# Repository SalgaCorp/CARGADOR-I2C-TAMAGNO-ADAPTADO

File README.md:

# CARGADOR-TAMAÑO-ADAPTADO

**Objetivos**:

1.- Open Source.

2.- Que el tamaño sea similar al cargador TP4056 para usar en proyectos ya existentes.

3.- Que tenga monitoreo de variables de batería: voltaje, %carga, etc.

# **Contenido del repositorio**:

PCB
Datasheet
Fotos

# *Documentation*:

Usa los siguientes componentes importantes:

Datasheet (BQ24075 Charger)

[bq24075.pdf](https://github.com/SalgaCorp/CARGADOR-TAMAGNO-ADAPTADO/files/10971589/bq24075.pdf)

Datasheet (BQ27441-G1 Fuel Gauge)

[bq27441-g1.pdf](https://github.com/SalgaCorp/CARGADOR-TAMAGNO-ADAPTADO/files/10971591/bq27441-g1.pdf)

Para monitoreo de variables de batería usar la siguiente libreria y ejemplos de cortesia de SpurkFun:  

https://github.com/sparkfun/SparkFun_BQ27441_Arduino_Library

Comparacion de PCB con tamaño del cargador TP4056

# Product Versions: DEMO

Luego subiré la pcb armada completamente.

# License Information
This product is open source!

# Contact Us
Call or WhatsApp 
https://api.whatsapp.com/send?phone=56966814899

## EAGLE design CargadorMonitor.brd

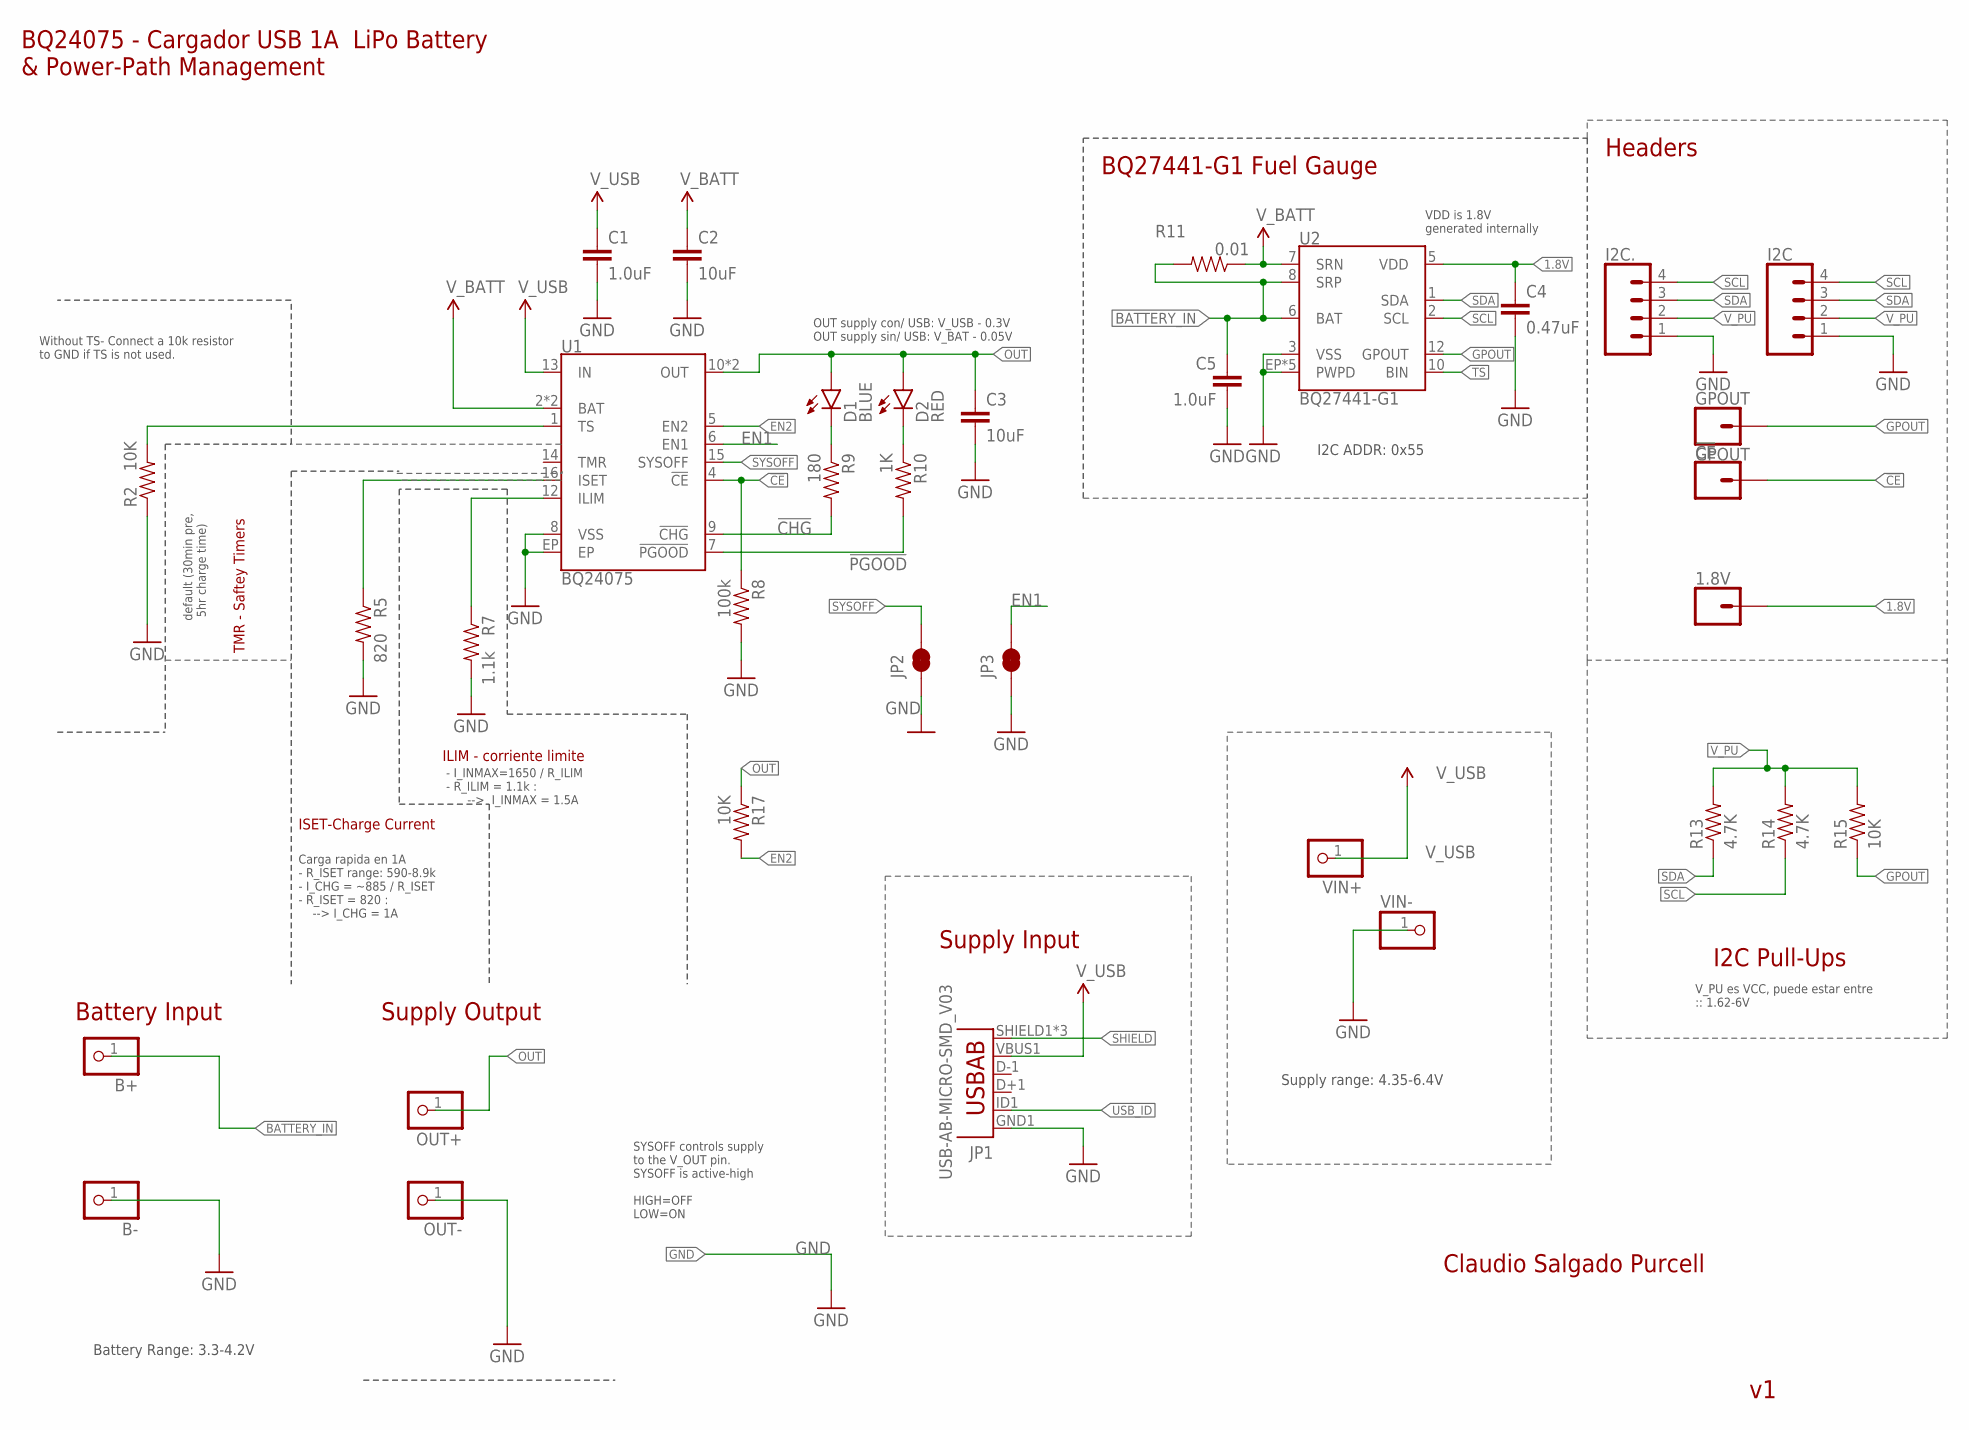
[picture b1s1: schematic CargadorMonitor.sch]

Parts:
1.8V: CONN_01PTH_NO_SILK_SMALL; 1X01_SMALL
!CE!: CONN_01PTH_NO_SILK_SMALL; 1X01_SMALL
B+: PINHD-1X1; 1X01
B-: PINHD-1X1; 1X01
C1: 1.0uF; 1206-CAP
C2, C3: 10uF; 0805-CAP
C4: 0.47uF; 0603-CAP
C5: 1.0uF; 0603-CAP
D1: BLUE; LED-0603
D2: RED; LED-0603
GPOUT: GPOUT; 1X01_SMALL
I2C: CONN_04SMD2; JST04_1MM_RA
I2C.: CONN_041.27MM; 1X04_1.27MM
JP1: USB-AB-MICRO-SMD_V03
JP2, JP3: JUMPER-SMT_2_NC_TRACE_SILK; SMT-JUMPER_2_NC_TRACE_SILK
OUT+: PINHD-1X1; 1X01
OUT-: PINHD-1X1; 1X01
R2, R15, R17: 10K; 0603-RES
R5: 820; 0603-RES
R7: 1.1k; 0603-RES
R8: 100k; 0603-RES
R9: 180; 0603-RES
R10: 1K; 0603-RES
R11: 0.01; 1206
R13, R14: 4.7K; 0603-RES
U1: BQ24075; PVQFN-N16
U2: BQ27441-G1; PDSO-N12
VIN+: PINHD-1X1; 1X01
VIN-: PINHD-1X1; 1X01

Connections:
1.8V: 1.8V.P$1, C4.1, U2.5 (VDD)
!CE!: !CE!.P$1, R8.1, U1.4 (!CE!)
!CHG!: R9.2, U1.9 (!CHG!)
!PGOOD!: R10.2, U1.7 (!PGOOD!)
BATTERY_IN: B+.1, C5.1, R11.2, U2.6 (BAT), U2.8 (SRP)
EN1: JP3.2, U1.6 (EN1)
EN2: R17.2, U1.5 (EN2)
GND: B-.1, C1.2, C2.2, C3.2, C4.2, C5.2, I2C.1, I2C..1, JP1.GND1 (GND), JP2.1, JP3.1, OUT-.1, R2.1, R5.2, R7.2, R8.2, U1.8 (VSS), U1.EP, U2.3 (VSS), U2.EP (PWPD), U2.EP1 (PWPD), U2.EP2 (PWPD), U2.EP3 (PWPD), U2.EP4 (PWPD), VIN-.1
GPOUT: GPOUT.P$1, R15.1, U2.12 (GPOUT)
ILIM: R7.1, U1.12 (ILIM)
ISET: R5.1, U1.16 (ISET)
unnamed: D1.C, R9.1
unnamed: D2.C, R10.1
OUT: C3.1, D1.A, D2.A, OUT+.1, R17.1, U1.10 (OUT), U1.11 (OUT)
SCL: I2C.4, I2C..4, R14.1, U2.2 (SCL)
SDA: I2C.3, I2C..3, R13.1, U2.1 (SDA)
SHIELD: JP1.SHIELD1 (SHIELD), JP1.SHIELD2 (SHIELD), JP1.SHIELD3 (SHIELD)
SYSOFF: JP2.2, U1.15 (SYSOFF)
TS: R2.2, U1.1 (TS), U2.10 (BIN)
USB_ID: JP1.ID1 (USBID)
V_BATT: C2.1, R11.1, U1.2 (BAT), U1.3 (BAT), U2.7 (SRN)
V_PU: I2C.2, I2C..2, R13.2, R14.2, R15.2
V_USB: C1.1, JP1.VBUS1 (VBUS), U1.13 (IN), VIN+.1

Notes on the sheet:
Carga rapida en 1A - R_ISET range: 590-8.9k - I_CHG = ~885 / R_ISET - R_ISET = 820 : --> I_CHG = 1A
- I_INMAX=1650 / R_ILIM - R_ILIM = 1.1k : --> I_INMAX = 1.5A
Supply Input
Battery Input
Supply Output
BQ24075 - Cargador USB 1A LiPo Battery & Power-Path Management
I2C Pull-Ups
BQ27441-G1 Fuel Gauge
Headers
Claudio Salgado Purcell
SYSOFF controls supply to the V_OUT pin. SYSOFF is active-high HIGH=OFF LOW=ON
ILIM - corriente limite
ISET-Charge Current
TMR - Saftey Timers
default (30min pre, 5hr charge time)
Without TS- Connect a 10k resistor to GND if TS is not used.
V_PU es VCC, puede estar entre :: 1.62-6V
Supply range: 4.35-6.4V
VDD is 1.8V generated internally
OUT supply con/ USB: V_USB - 0.3V OUT supply sin/ USB: V_BAT - 0.05V
I2C ADDR: 0x55
Battery Range: 3.3-4.2V

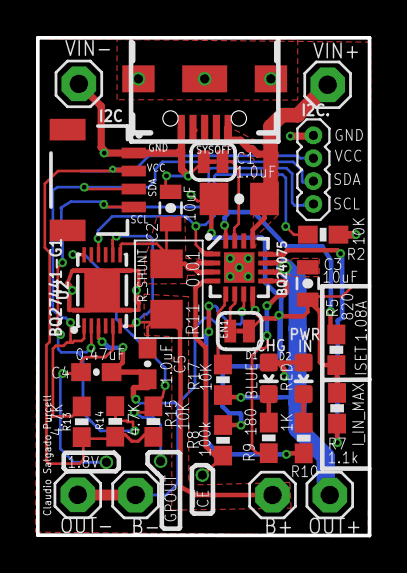
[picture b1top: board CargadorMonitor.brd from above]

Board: 2 copper layers, 18.4 x 27.6 mm, 34 parts (0 on the bottom side), 22 nets.

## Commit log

2023-03-14 DATASHEETS

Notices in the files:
parts and their libraries:
SparkFun-Connectors: Licensing: Creative Commons ShareAlike 4.0 International - https://creativecommons.org/licenses/by-sa/4.0
